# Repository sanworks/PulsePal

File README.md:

# PulsePal
Open source pulse train generator

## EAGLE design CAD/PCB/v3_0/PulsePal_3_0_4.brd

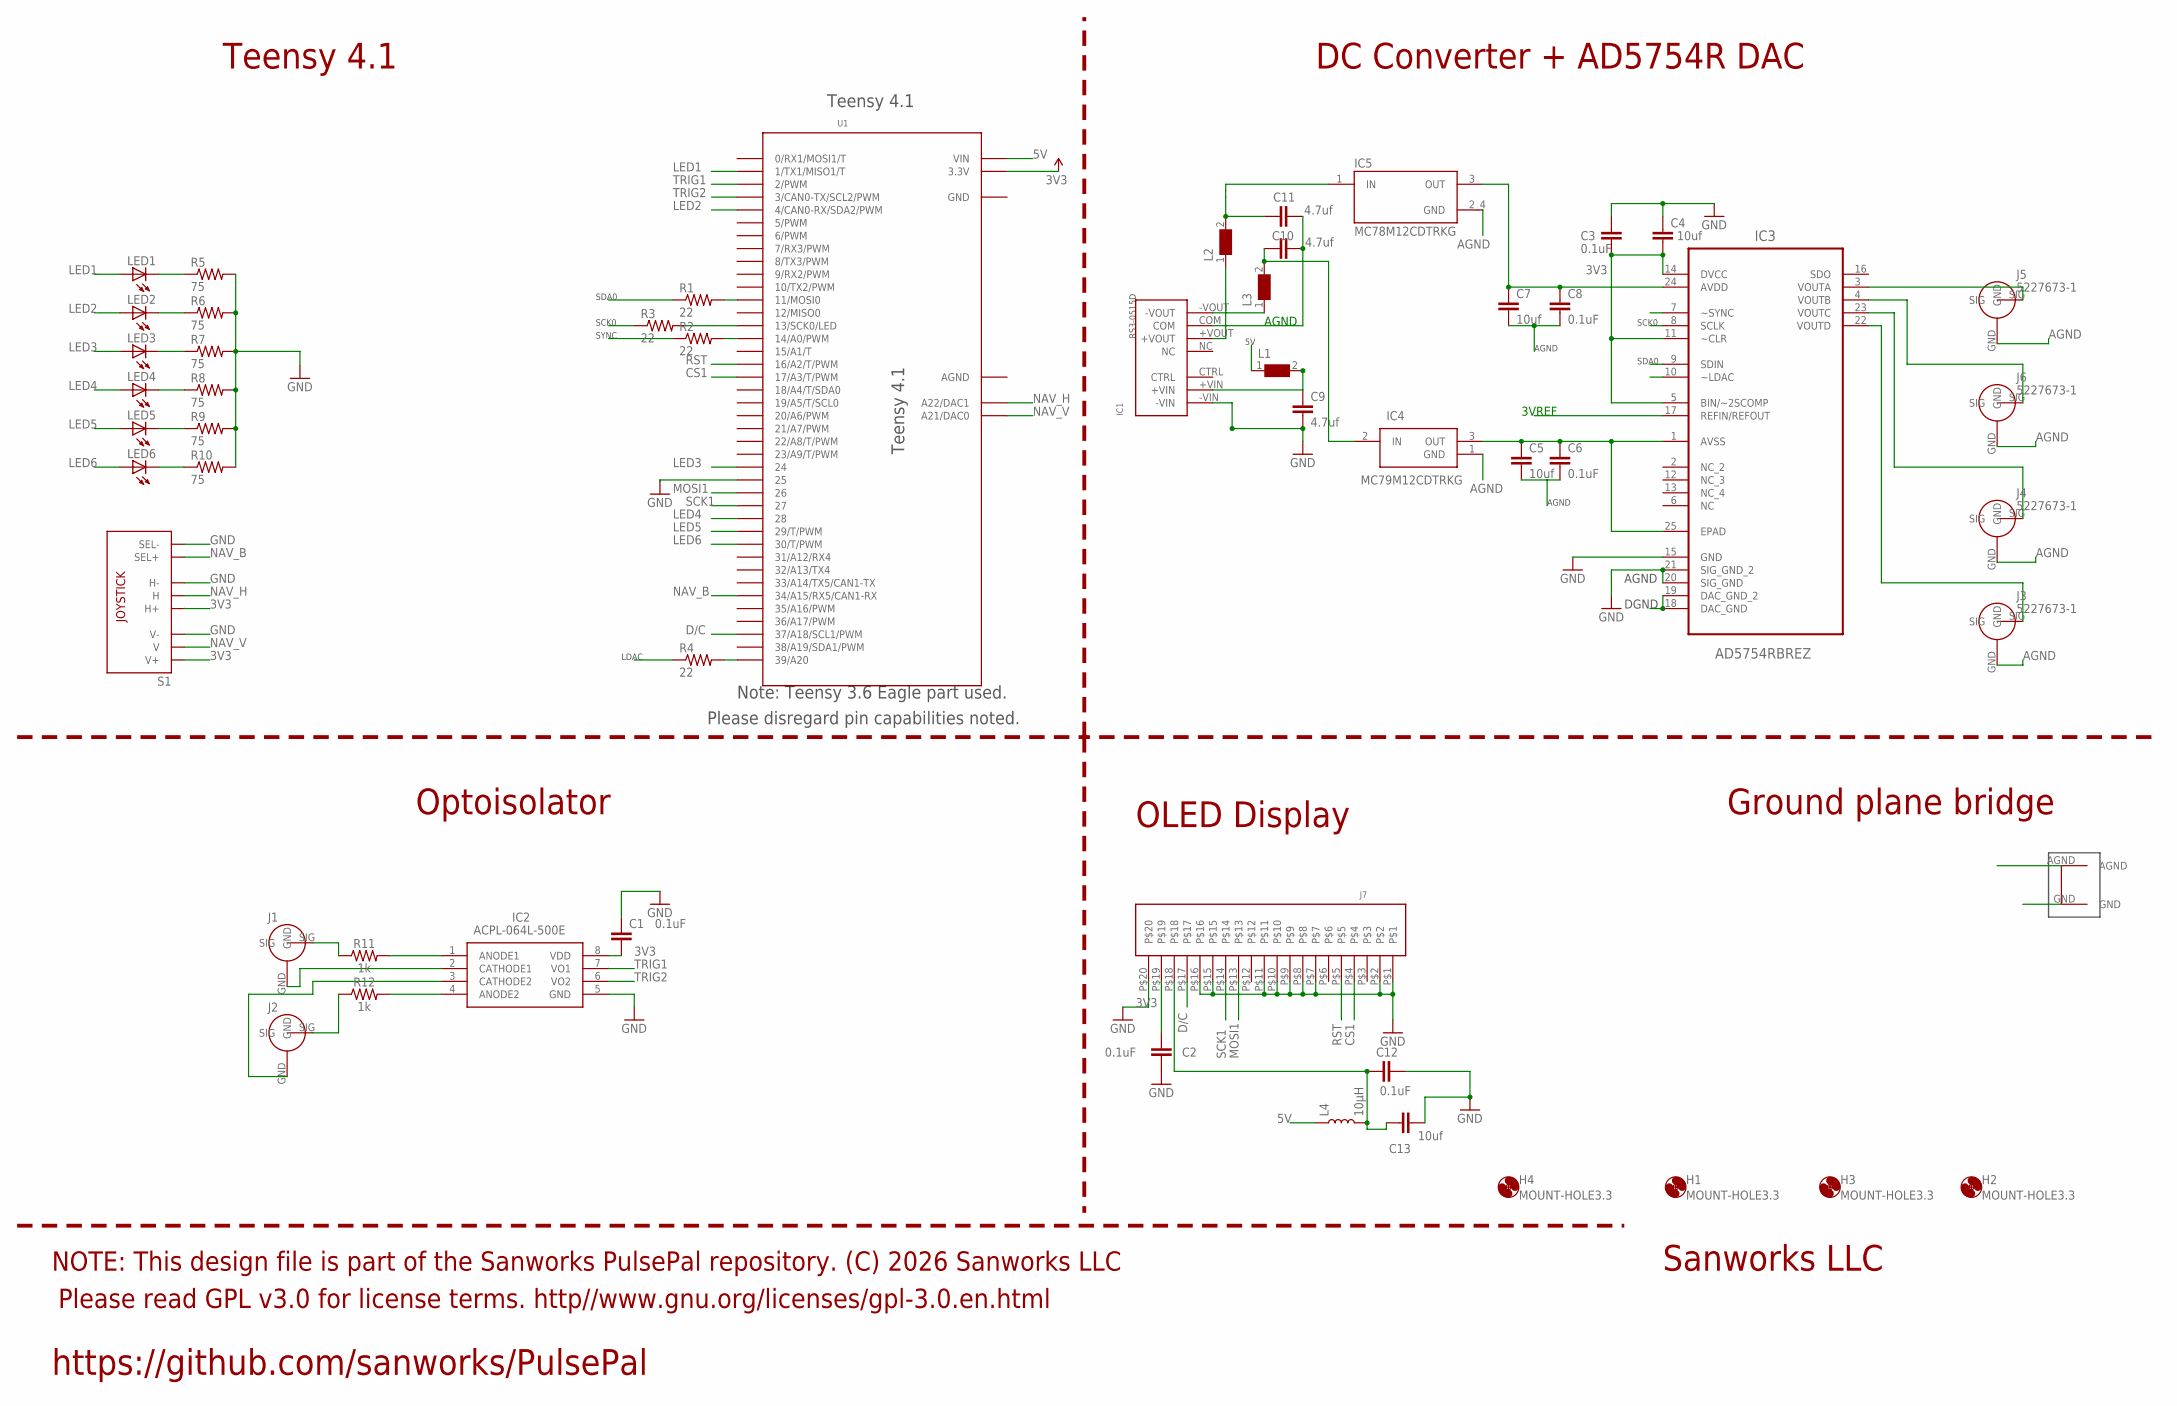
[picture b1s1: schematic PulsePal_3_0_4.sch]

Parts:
C1, C2, C3, C6, C8, C12: 0.1uF; 0805
C4, C5, C7, C13: 10uf; 1206@1
C9, C10, C11: 4.7uf; 1206@1
H1, H2, H3, H4: MOUNT-HOLE3.3; 3,3
IC1: RS3-0515D
IC2: ACPL-064L-500E; SOIC127P599X330-8N
IC3: AD5754RBREZ; SOP65P640X120-25N
IC4: MC79M12CDTRKG; NVD5117PLT4GVF01
IC5: MC78M12CDTRKG; VREG_MC78M12CDTRKG
J1, J2, J3, J4, J5, J6: 5227673-1; 52276731
J7: NHD-2.7-12864WDW3
L1, L2, L3: WE-CBF-742792118_1206; 1206
L4: 10μH; 0806
LED1, LED2, LED3, LED4, LED5, LED6: LEDCHIPLED_1206; CHIPLED_1206
R1, R2, R3, R4: 22; 1206
R5, R6, R7, R8, R9, R10: 75; 1206
R11, R12: 1k; 1206
S1: JOYSTICKPTH; JOYSTICK
U1: TEENSY_3.6_DIL
U$6: GNDPLANESHRT

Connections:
3V3: C1.2, C2.1, C3.2, C4.2, IC2.8 (VDD), IC3.5 (BIN/~2SCOMP), IC3.11 (~CLR), IC3.14 (DVCC), J7.P$19, S1.H1 (H+), S1.V1 (V+), U1.3.3V, U1.3.3V3 (3.3V)
3VREF: IC3.17 (REFIN/REFOUT)
5V: L1.1, L4.1, U1.VIN
AGND: C5.2, C6.2, C7.2, C8.2, C10.1, C11.2, IC1.COM, IC3.18 (DAC_GND), IC3.19 (DAC_GND_2), IC3.20 (SIG_GND), IC3.21 (SIG_GND_2), IC4.1 (GND), IC5.2_4 (GND), J3.GND, J4.GND, J5.GND, J6.GND, U1.AGND, U$6.AGND
CS1: J7.P$4, U1.17/A3 (17/A3/T/PWM)
D/C: J7.P$17, U1.37/A18 (37/A18/SCL1/PWM)
GND: C1.1, C2.2, C3.1, C4.1, C9.2, C12.2, C13.2, IC1.-VIN, IC2.5 (GND), IC3.15 (GND), J7.P$1, J7.P$2, J7.P$7, J7.P$8, J7.P$9, J7.P$10, J7.P$11, J7.P$15, J7.P$16, J7.P$20, R5.2, R6.2, R7.2, R8.2, R9.2, R10.2, S1.B2A (SEL-), S1.H3 (H-), S1.V3 (V-), U1.25, U1.GND, U1.GND1 (GND), U$6.GND
LDAC: IC3.10 (~LDAC), R4.1
LED1: LED1.A, U1.1 (1/TX1/MISO1/T)
LED2: LED2.A, U1.4 (4/CAN0-RX/SDA2/PWM)
LED3: LED3.A, U1.24
LED4: LED4.A, U1.28
LED5: LED5.A, U1.29 (29/T/PWM)
LED6: LED6.A, U1.30 (30/T/PWM)
MOSI1: J7.P$13, U1.26
unnamed: IC2.1 (ANODE1), R11.2
unnamed: J1.SIG, R11.1
unnamed: IC2.4 (ANODE2), R12.2
unnamed: J2.SIG, R12.1
unnamed: IC2.2 (CATHODE1), J1.GND
unnamed: IC2.3 (CATHODE2), J2.GND
unnamed: LED1.C, R5.1
unnamed: LED2.C, R6.1
unnamed: IC3.3 (VOUTA), J5.SIG
unnamed: IC3.4 (VOUTB), J6.SIG
unnamed: IC3.23 (VOUTC), J4.SIG
unnamed: IC3.22 (VOUTD), J3.SIG
unnamed: R1.2, U1.11 (11/MOSI0)
unnamed: R3.2, U1.13 (13/SCK0/LED)
unnamed: IC1.-VOUT, L3.1
unnamed: IC1.+VOUT, L2.1
unnamed: R2.2, U1.14/A0 (14/A0/PWM)
unnamed: R4.2, U1.39/A20
unnamed: LED3.C, R7.1
unnamed: LED4.C, R8.1
unnamed: LED5.C, R9.1
unnamed: LED6.C, R10.1
unnamed: C10.2, IC5.1 (IN), L2.2
unnamed: C11.1, IC4.2 (IN), L3.2
unnamed: C12.1, C13.1, J7.P$18, L4.2
unnamed: C9.1, IC1.+VIN, L1.2
NAV_B: S1.B1A (SEL+), U1.34/A15 (34/A15/RX5/CAN1-RX)
NAV_H: S1.H2 (H), U1.A22 (A22/DAC1)
NAV_V: S1.V2 (V), U1.A21 (A21/DAC0)
RST: J7.P$5, U1.16/A2 (16/A2/T/PWM)
SCK0: IC3.8 (SCLK), R3.1
SCK1: J7.P$14, U1.27
SDA0: IC3.9 (SDIN), R1.1
SYNC: IC3.7 (~SYNC), R2.1
TRIG1: IC2.7 (VO1), U1.2 (2/PWM)
TRIG2: IC2.6 (VO2), U1.3 (3/CAN0-TX/SCL2/PWM)
VDD: C7.1, C8.1, IC3.24 (AVDD), IC5.3 (OUT)
VSS: C5.1, C6.1, IC3.1 (AVSS), IC3.25 (EPAD), IC4.3 (OUT)

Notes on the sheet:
AGND
SCK0
SDA0
DGND
SYNC
LDAC
3VREF
Teensy 4.1
DC Converter + AD5754R DAC
Ground plane bridge
Please read GPL v3.0 for license terms. http//www.gnu.org/licenses/gpl-3.0.en.html
NOTE: This design file is part of the Sanworks PulsePal repository. (C) 2026 Sanworks LLC
Sanworks LLC
https://github.com/sanworks/PulsePal
Note: Teensy 3.6 Eagle part used.
Please disregard pin capabilities noted.
OLED Display
Optoisolator

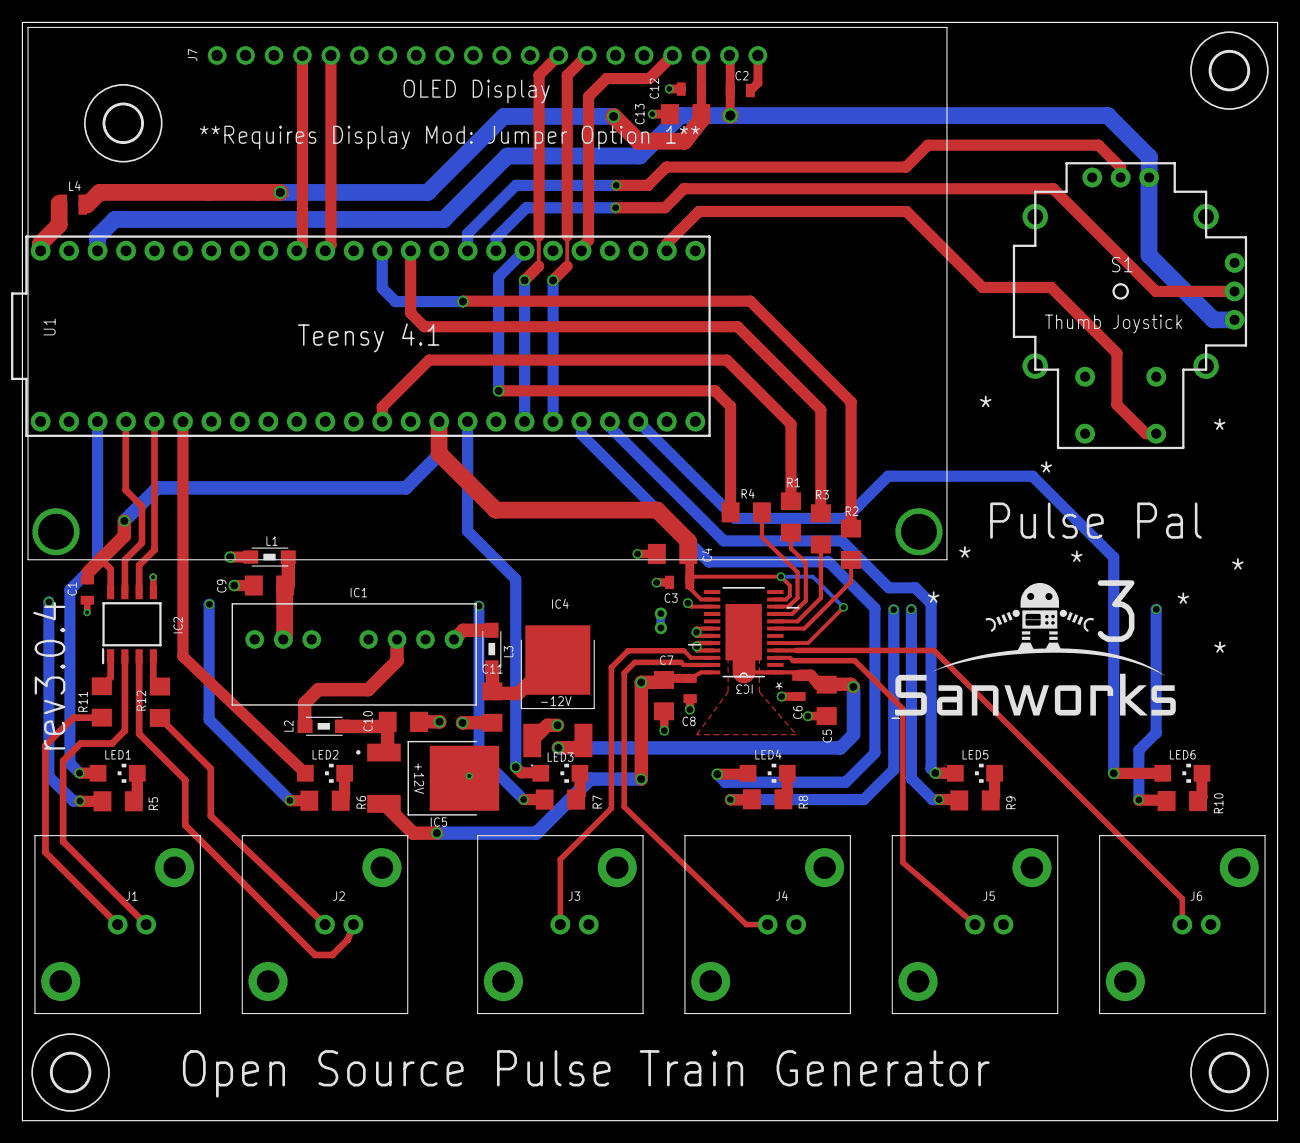
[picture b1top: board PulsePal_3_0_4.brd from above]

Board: 4 copper layers, 112.0 x 98.0 mm, 55 parts (0 on the bottom side), 52 nets.

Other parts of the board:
U$2: SANWORKS_LOGO

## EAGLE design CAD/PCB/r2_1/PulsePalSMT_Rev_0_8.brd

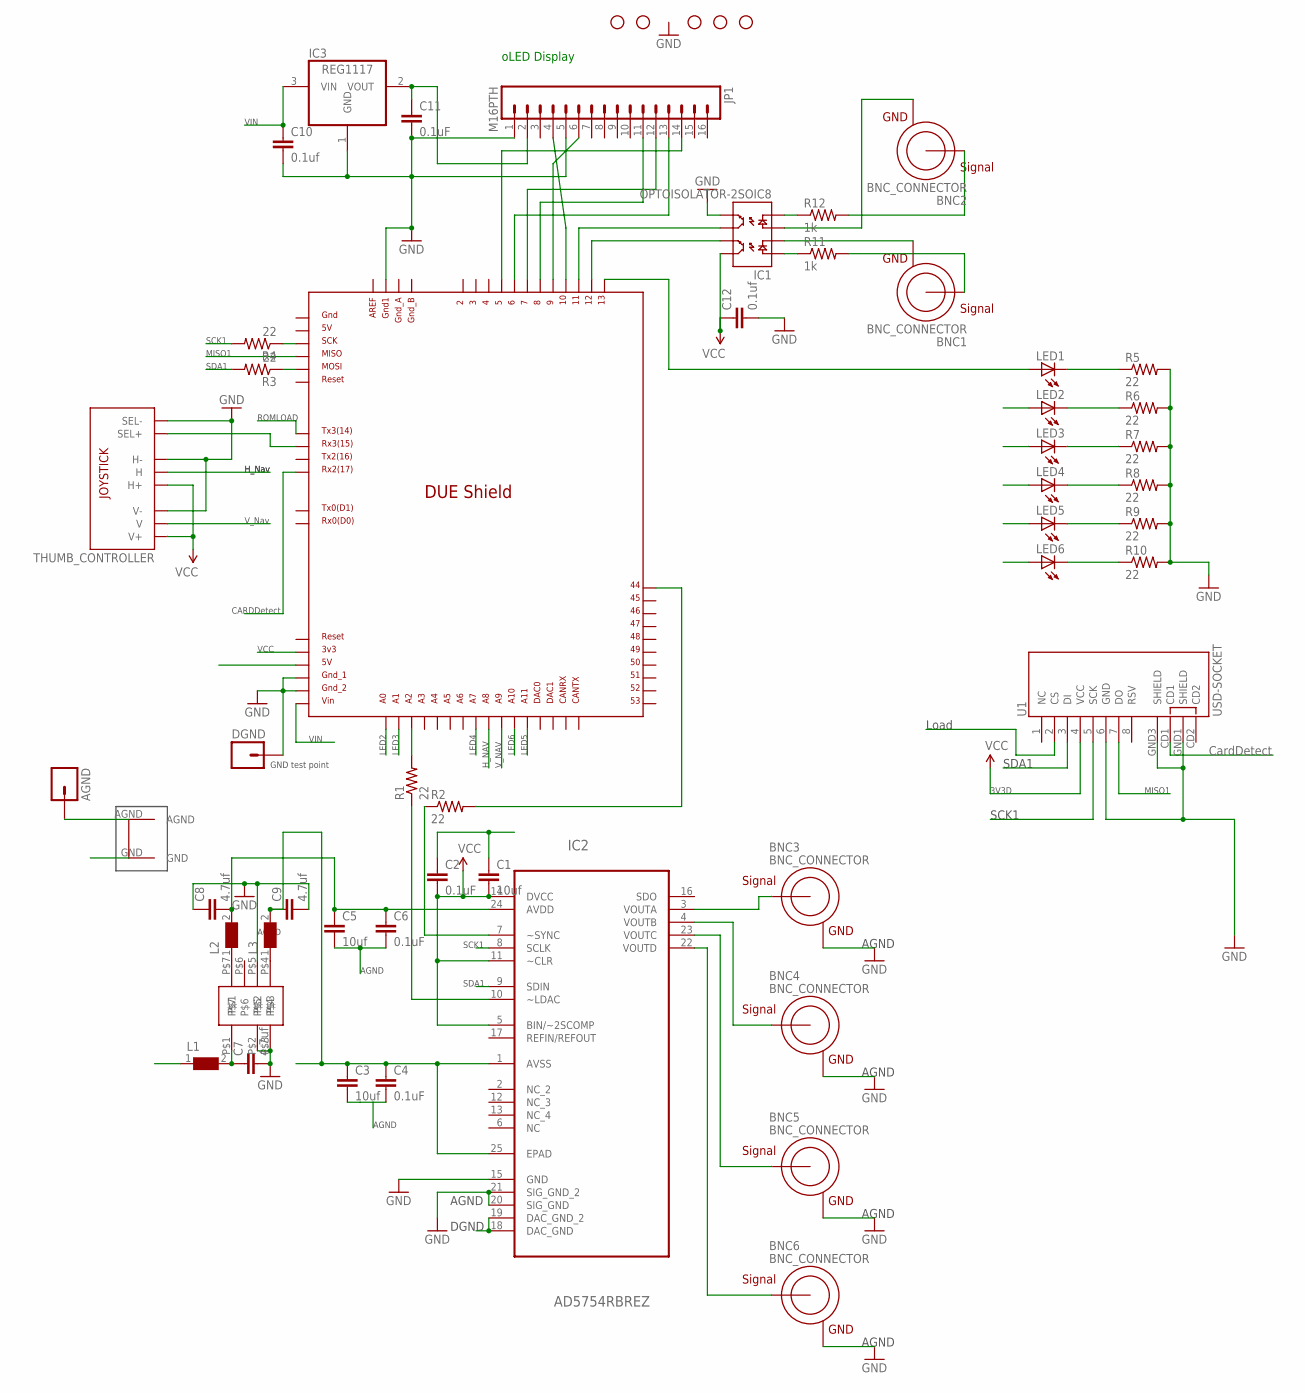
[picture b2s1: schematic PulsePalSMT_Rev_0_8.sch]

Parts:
AGND: M01PTH; 1X01
ARDUINO: DUE(NORMAL)
BNC1, BNC2, BNC3, BNC4, BNC5, BNC6: BNC_CONNECTOR
C1, C3, C5: 10uf; 1206@1
C2, C4, C6, C11: 0.1uF; 0805
C7, C8, C9: 4.7uf; 1206@1
C10: 0.1uf; 0805
C12: 0.1uf; 1206@1
DGND: M01PTH; 1X01
IC1: OPTOISOLATOR-2SOIC8; SO08-2
IC2: AD5754RBREZ; SOP65P640X120-25N
IC3: REG1117; SOT223
JP1: M16PTH; 1X16
JP2, JP5, JP6, JP8, JP9: STAND-OFF
L1, L2, L3: WE-CBF-742792118_1206; 1206
LED1, LED2, LED3, LED4, LED5, LED6: LEDCHIPLED_1206; CHIPLED_1206
R1, R2, R3, R4, R5, R6, R7, R8, R9, R10: 22; 1206
R11, R12: 1k; 1206
THUMB_CONTROLLER: JOYSTICKPTH; JOYSTICK
U1: USD-SOCKET; MICROSD_1:1
U2: TDK_LAMBDA_5_TO_BI_12_125MA
U$6: GNDPLANESHRT

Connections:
5V: ARDUINO.5V, C1.2, C2.2, IC2.5 (BIN/~2SCOMP), IC2.11 (~CLR), IC2.14 (DVCC), L1.1
AGND: AGND.1, BNC3.GND, BNC4.GND, BNC5.GND, BNC6.GND, C3.2, C4.2, C5.2, C6.2, IC2.15 (GND), IC2.18 (DAC_GND), IC2.19 (DAC_GND_2), IC2.20 (SIG_GND), IC2.21 (SIG_GND_2), U$6.AGND
CARDDETECT: ARDUINO.RX2, U1.CD1
GND: ARDUINO.GND1, ARDUINO.GND_1, ARDUINO.GND_2, C1.1, C2.1, C7.2, C8.1, C9.2, C10.2, C11.2, C12.2, DGND.1, IC1.5 (EM2), IC3.1 (GND), JP1.1, JP1.5, R5.2, R6.2, R7.2, R8.2, R9.2, R10.2, THUMB_CONTROLLER.B2A (SEL-), THUMB_CONTROLLER.H3 (H-), THUMB_CONTROLLER.V3 (V-), U1.6 (GND), U1.GND1 (SHIELD), U1.GND3 (SHIELD), U2.P$2, U2.P$3, U2.P$5, U$6.GND
H_NAV: ARDUINO.A8, THUMB_CONTROLLER.H2 (H)
LED2: ARDUINO.A0, LED2.A
LED3: ARDUINO.A1, LED3.A
LED4: ARDUINO.A7, LED4.A
LED5: ARDUINO.A11, LED5.A
LED6: ARDUINO.A10, LED6.A
MISO1: ARDUINO.MISO_ICSP, U1.7 (DO)
unnamed: L2.1, U2.P$7
unnamed: L3.1, U2.P$4
unnamed: BNC3.SIGNAL, IC2.3 (VOUTA)
unnamed: BNC4.SIGNAL, IC2.4 (VOUTB)
unnamed: BNC5.SIGNAL, IC2.23 (VOUTC)
unnamed: BNC6.SIGNAL, IC2.22 (VOUTD)
unnamed: BNC1.GND, IC1.2 (C1)
unnamed: BNC1.SIGNAL, R11.2
unnamed: BNC2.GND, IC1.3 (A2)
unnamed: BNC2.SIGNAL, R12.2
unnamed: ARDUINO.SCK_ICSP, R4.1
unnamed: ARDUINO.MOSI_ICSP, R3.1
unnamed: ARDUINO.44, R2.2
unnamed: ARDUINO.A2, R1.2
unnamed: IC2.7 (~SYNC), R2.1
unnamed: IC2.10 (~LDAC), R1.1
unnamed: ARDUINO.RX3, THUMB_CONTROLLER.B1A (SEL+)
unnamed: ARDUINO.11, IC1.6 (CL2)
unnamed: C11.1, IC3.2 (VOUT), JP1.2
unnamed: LED1.C, R5.1
unnamed: LED2.C, R6.1
unnamed: LED3.C, R7.1
unnamed: LED4.C, R8.1
unnamed: LED5.C, R9.1
unnamed: LED6.C, R10.1
unnamed: IC1.1 (A1), R11.1
unnamed: IC1.4 (C2), R12.1
unnamed: ARDUINO.12, IC1.7 (EM1)
unnamed: ARDUINO.5, JP1.14
unnamed: ARDUINO.13, LED1.A
unnamed: ARDUINO.10, JP1.4
unnamed: ARDUINO.9, JP1.6
unnamed: ARDUINO.8, JP1.11
unnamed: ARDUINO.7, JP1.12
unnamed: ARDUINO.6, JP1.13
unnamed: C5.1, C6.1, C8.2, IC2.24 (AVDD), L2.2
unnamed: C3.1, C4.1, C9.1, IC2.1 (AVSS), IC2.25 (EPAD), L3.2
unnamed: C7.1, L1.2, U2.P$1
ROMLOAD: ARDUINO.TX3, U1.2 (CS)
SCK1: IC2.8 (SCLK), R4.2, U1.5 (SCK)
SDA1: IC2.9 (SDIN), R3.2, U1.3 (DI)
VCC: ARDUINO.3V3, C12.1, IC1.8 (CL1), THUMB_CONTROLLER.H1 (H+), THUMB_CONTROLLER.V1 (V+), U1.4 (VCC)
VIN: ARDUINO.VIN, C10.1, IC3.3 (VIN)
V_NAV: ARDUINO.A9, THUMB_CONTROLLER.V2 (V)

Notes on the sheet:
oLED Display
AGND
SCK1
SDA1
DGND
VCC
ROMLOAD
LED2
LED3
LED4
LED5
LED6
GND test point
H_Nav
V_Nav
MISO1
H_NAV
V_NAV
VIN
3V3D
Load
CardDetect
CARDDetect

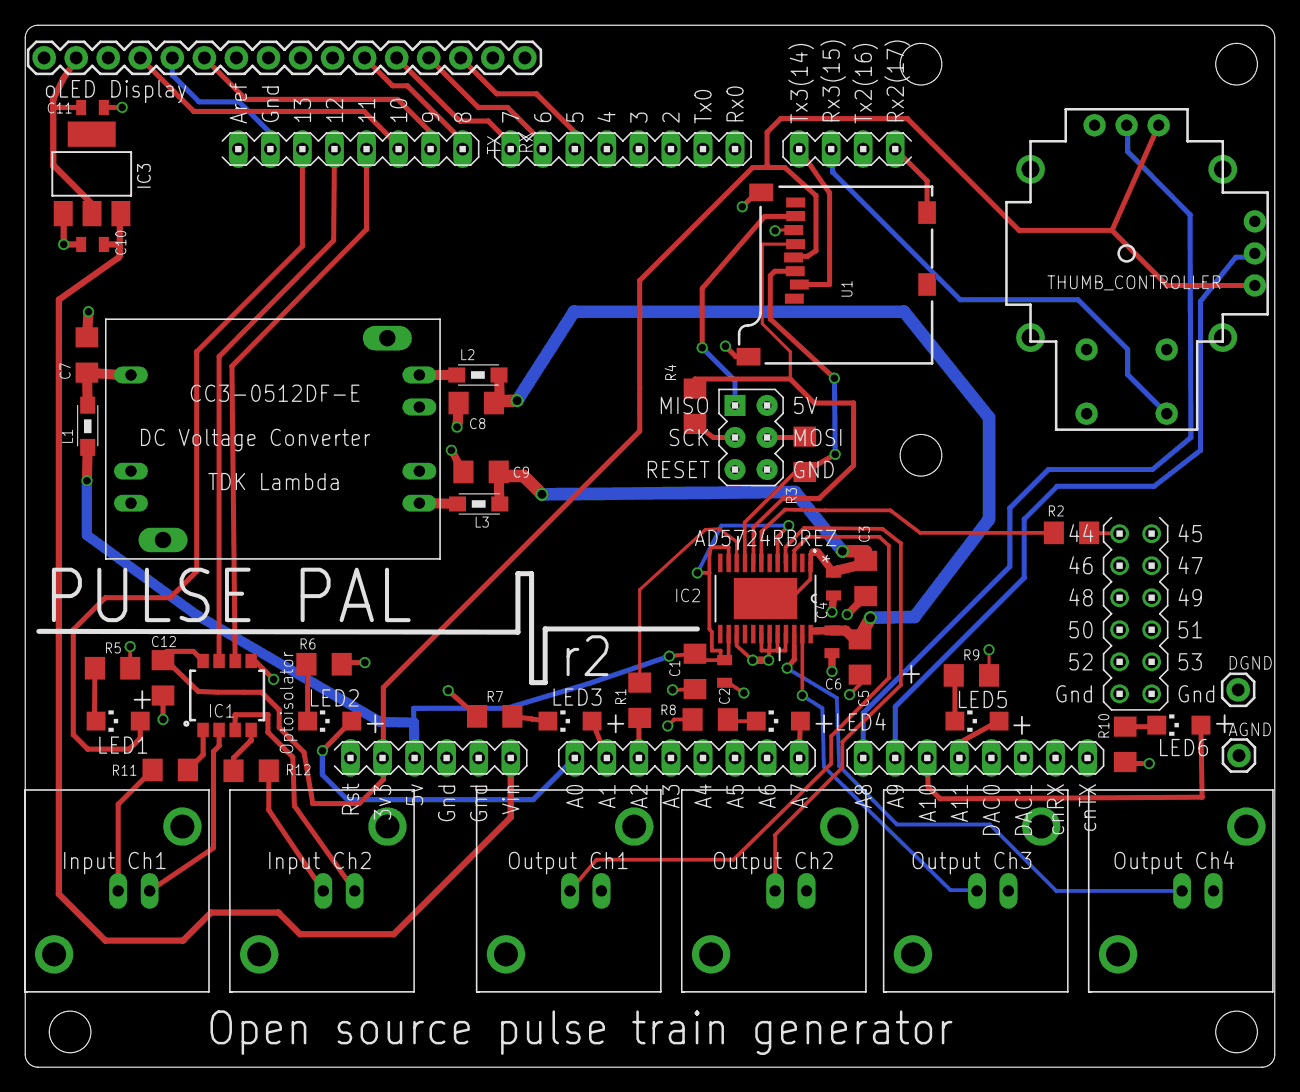
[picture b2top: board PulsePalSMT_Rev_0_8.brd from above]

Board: 4 copper layers, 99.0 x 82.6 mm, 55 parts (0 on the bottom side), 55 nets.

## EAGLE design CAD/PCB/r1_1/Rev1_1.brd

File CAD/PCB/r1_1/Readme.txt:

----------------------------------------------------------------------------

The files in this folder are part of the Sanworks Pulse Pal repository
Copyright (C) 2016 Sanworks LLC, Sound Beach, New York, USA

----------------------------------------------------------------------------

These design files are free software: you can redistribute and/or modify
them under the terms of the GNU General Public License as published by
the Free Software Foundation, version 3.

These files are distributed  WITHOUT ANY WARRANTY and without even the 
implied warranty of MERCHANTABILITY or FITNESS FOR A PARTICULAR PURPOSE.  
See the GNU General Public License for more details.

You should have received a copy of the GNU General Public License
along with these files. If not, see <http://www.gnu.org/licenses/>.

-----------------------------------------------------------------------------

*Instructions*

The schematic Rev_X.X.sch,
and the circuit board design file Rev_X.X.brd,
can be opened with Cadsoft Eagle:
http://www.cadsoftusa.com/

The GERBER files are pre-compiled CAM files for circuit board manufacturing with SeeedStudio's fusion PCB service.
USA: http://www.seeedstudio.com/service/index.php?r=upcb
Global: http://www.seeedstudio.com/service/index.php?r=pcb

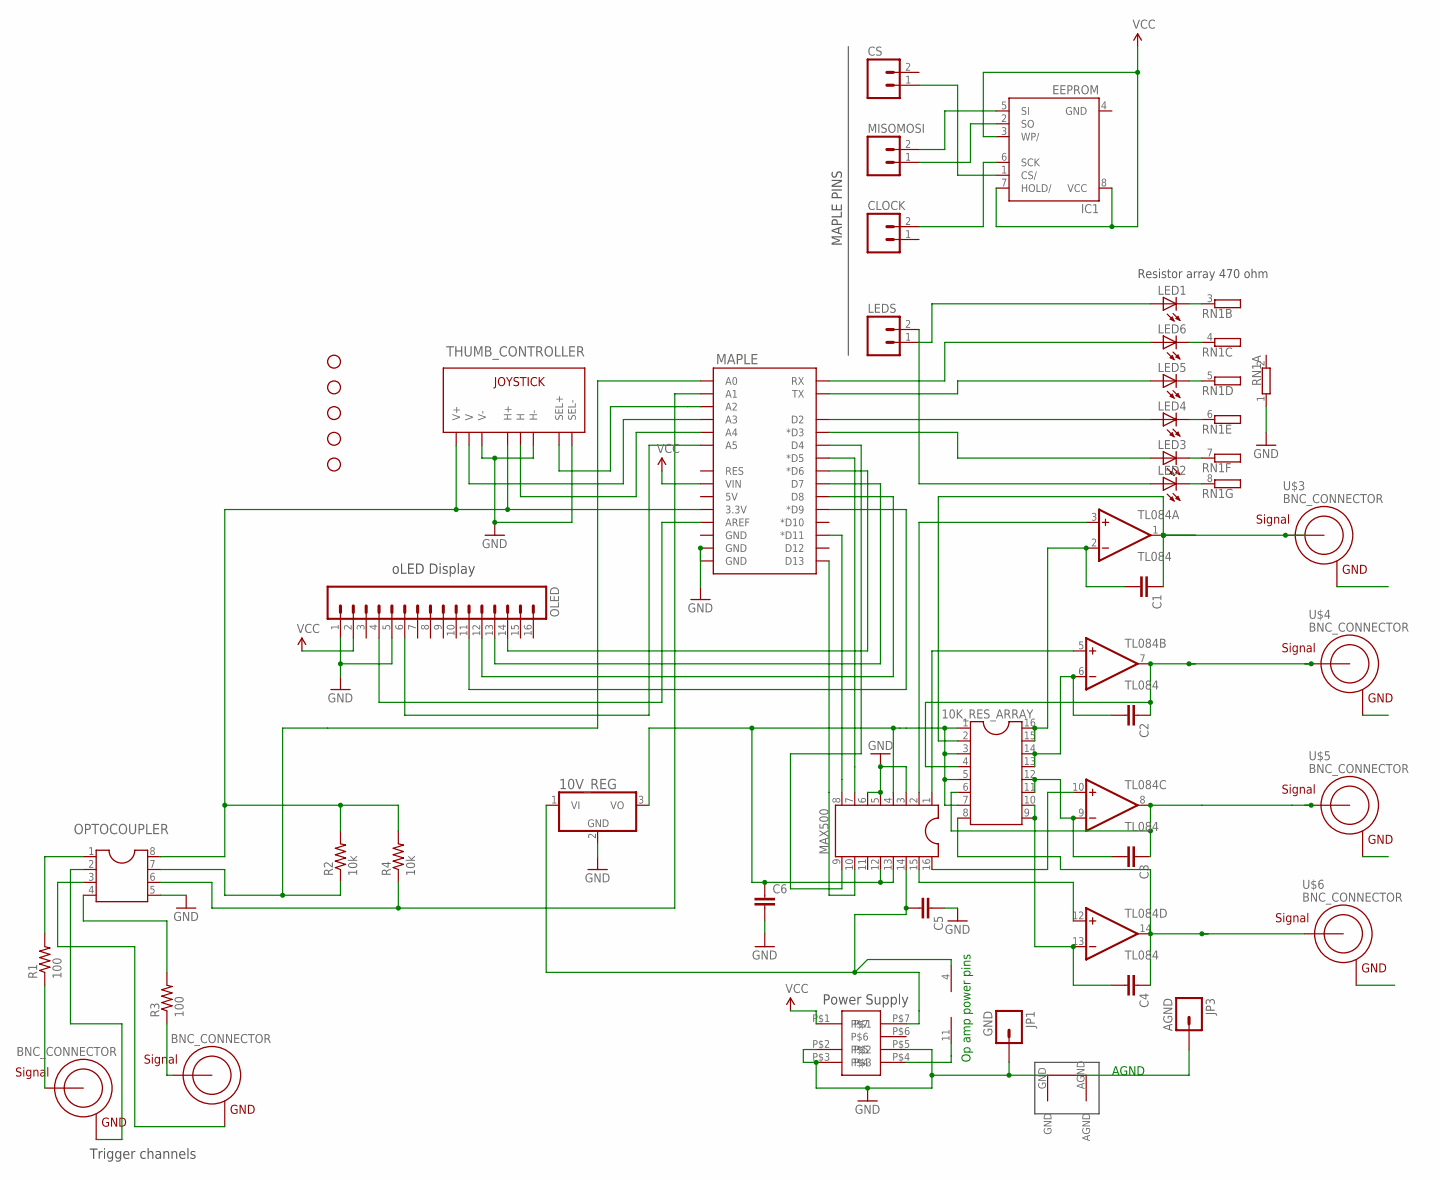
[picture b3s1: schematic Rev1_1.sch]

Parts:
10K_RES_ARRAY: DIL16
10V_REG: 7805T; TO220H
C1, C2, C3, C4, C5, C6: CAPPTH; CAP-PTH-SMALL
CLOCK: M02PTH; 1X02
CS: M02PTH; 1X02
IC1: EEPROM; DIL08
JP1: GND; 1X01
JP2, JP5, JP6, JP8, JP9: STAND-OFF
JP3: AGND; 1X01
LED1, LED2, LED3, LED4, LED5, LED6: LED3MM
LEDS: M02PTH; 1X02
MAPLE: ARDUINO_SHIELDNOHOLESORLABELS; DUEMILANOVE_SHIELD_NOHOLES_NOLABELS
MAX500: DIL16
MISOMOSI: M02PTH; 1X02
OLED: M16PTH; 1X16
OPTOCOUPLER: DIL8; DIL08
R1, R3: 100; AXIAL-0.3
R2, R4: 10k; AXIAL-0.3
RN1: GE07R; SIL8
THUMB_CONTROLLER: JOYSTICKPTH; JOYSTICK
TL084: TL084; DIL14
U$1, U$2, U$3, U$4, U$5, U$6: BNC_CONNECTOR
U$7: GNDPLANESHRT
U$8: TDK_LAMBDA_5_TO_BI_12_125MA

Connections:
AGND: JP3.1, U$3.GND, U$4.GND, U$5.GND, U$6.GND, U$7.AGND
GND: 10V_REG.2 (GND), C5.1, C6.2, IC1.4 (GND), JP1.1, MAPLE.GND@0 (GND), MAPLE.GND@1 (GND), MAX500.3, MAX500.5, MAX500.6, OLED.1, OLED.5, OPTOCOUPLER.5, RN1.1, THUMB_CONTROLLER.B2A (SEL-), THUMB_CONTROLLER.H3 (H-), THUMB_CONTROLLER.V3 (V-), U$7.GND, U$8.P$2, U$8.P$3, U$8.P$5
unnamed: LED6.A, MAPLE.RX
unnamed: LED5.A, MAPLE.TX
unnamed: LED4.A, MAPLE.D2
unnamed: LED3.A, MAPLE.D3 (*D3)
unnamed: MAPLE.D11 (*D11), MAX500.8
unnamed: MAPLE.D13, MAX500.10
unnamed: MAPLE.AREF, OLED.4
unnamed: MAPLE.D4, MAX500.9
unnamed: MAPLE.D5 (*D5), MAX500.7
unnamed: MAPLE.D6 (*D6), OLED.14
unnamed: MAPLE.D7, OLED.13
unnamed: MAPLE.D8, OLED.12
unnamed: MAPLE.D9 (*D9), OLED.11
unnamed: MAPLE.A5, OLED.6
unnamed: MAPLE.A4, THUMB_CONTROLLER.H2 (H)
unnamed: MAPLE.A3, THUMB_CONTROLLER.V2 (V)
unnamed: MAPLE.A2, THUMB_CONTROLLER.B1A (SEL+)
unnamed: R1.P$1 (1), U$1.SIGNAL
unnamed: MAPLE.A0, OPTOCOUPLER.7, R2.P$1 (1)
unnamed: R3.P$1 (1), U$2.SIGNAL
unnamed: MAPLE.A1, OPTOCOUPLER.6, R4.P$1 (1)
unnamed: TL084.11 (V-), U$8.P$4
unnamed: MAX500.2, TL084.3 (+IN)
unnamed: MAX500.1, TL084.5 (+IN)
unnamed: 10V_REG.1 (VI), C5.2, MAX500.14, TL084.4 (V+), U$8.P$7
unnamed: 10K_RES_ARRAY.1, 10K_RES_ARRAY.3, 10K_RES_ARRAY.5, 10K_RES_ARRAY.7, 10V_REG.3 (VO), C6.1, MAX500.4, MAX500.12, MAX500.13
unnamed: MAX500.16, TL084.10 (+IN)
unnamed: MAX500.15, TL084.12 (+IN)
unnamed: 10K_RES_ARRAY.2, C1.1, TL084.1 (OUT), U$3.SIGNAL
unnamed: 10K_RES_ARRAY.4, C2.1, TL084.7 (OUT), U$4.SIGNAL
unnamed: 10K_RES_ARRAY.6, C3.1, TL084.8 (OUT), U$5.SIGNAL
unnamed: 10K_RES_ARRAY.8, C4.1, TL084.14 (OUT), U$6.SIGNAL
unnamed: LED1.A, LEDS.1
unnamed: LED2.A, LEDS.2
unnamed: LED2.K (C), RN1.8 (2)
unnamed: LED3.K (C), RN1.7 (2)
unnamed: LED4.K (C), RN1.6 (2)
unnamed: LED5.K (C), RN1.5 (2)
unnamed: LED6.K (C), RN1.4 (2)
unnamed: 10K_RES_ARRAY.15, 10K_RES_ARRAY.16, C1.2, TL084.2 (-IN)
unnamed: 10K_RES_ARRAY.13, 10K_RES_ARRAY.14, C2.2, TL084.6 (-IN)
unnamed: 10K_RES_ARRAY.11, 10K_RES_ARRAY.12, C3.2, TL084.9 (-IN)
unnamed: 10K_RES_ARRAY.9, 10K_RES_ARRAY.10, C4.2, TL084.13 (-IN)
unnamed: LED1.K (C), RN1.3 (2)
unnamed: OPTOCOUPLER.1, R1.P$2 (2)
unnamed: CS.1, IC1.1 (CS/)
unnamed: IC1.5 (SI), MISOMOSI.2
unnamed: IC1.2 (SO), MISOMOSI.1
unnamed: CLOCK.2, IC1.6 (SCK)
unnamed: OPTOCOUPLER.2, U$1.GND
unnamed: OPTOCOUPLER.4, R3.P$2 (2)
unnamed: OPTOCOUPLER.3, U$2.GND
unnamed: MAPLE.3.3V, OPTOCOUPLER.8, R2.P$2 (2), R4.P$2 (2), THUMB_CONTROLLER.H1 (H+), THUMB_CONTROLLER.V1 (V+)
VCC: IC1.3 (WP/), IC1.7 (HOLD/), IC1.8 (VCC), MAPLE.VIN, OLED.2, U$8.P$1

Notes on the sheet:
oLED Display
Power Supply
Op amp power pins
MAPLE PINS
Trigger channels
Resistor array 470 ohm
AGND

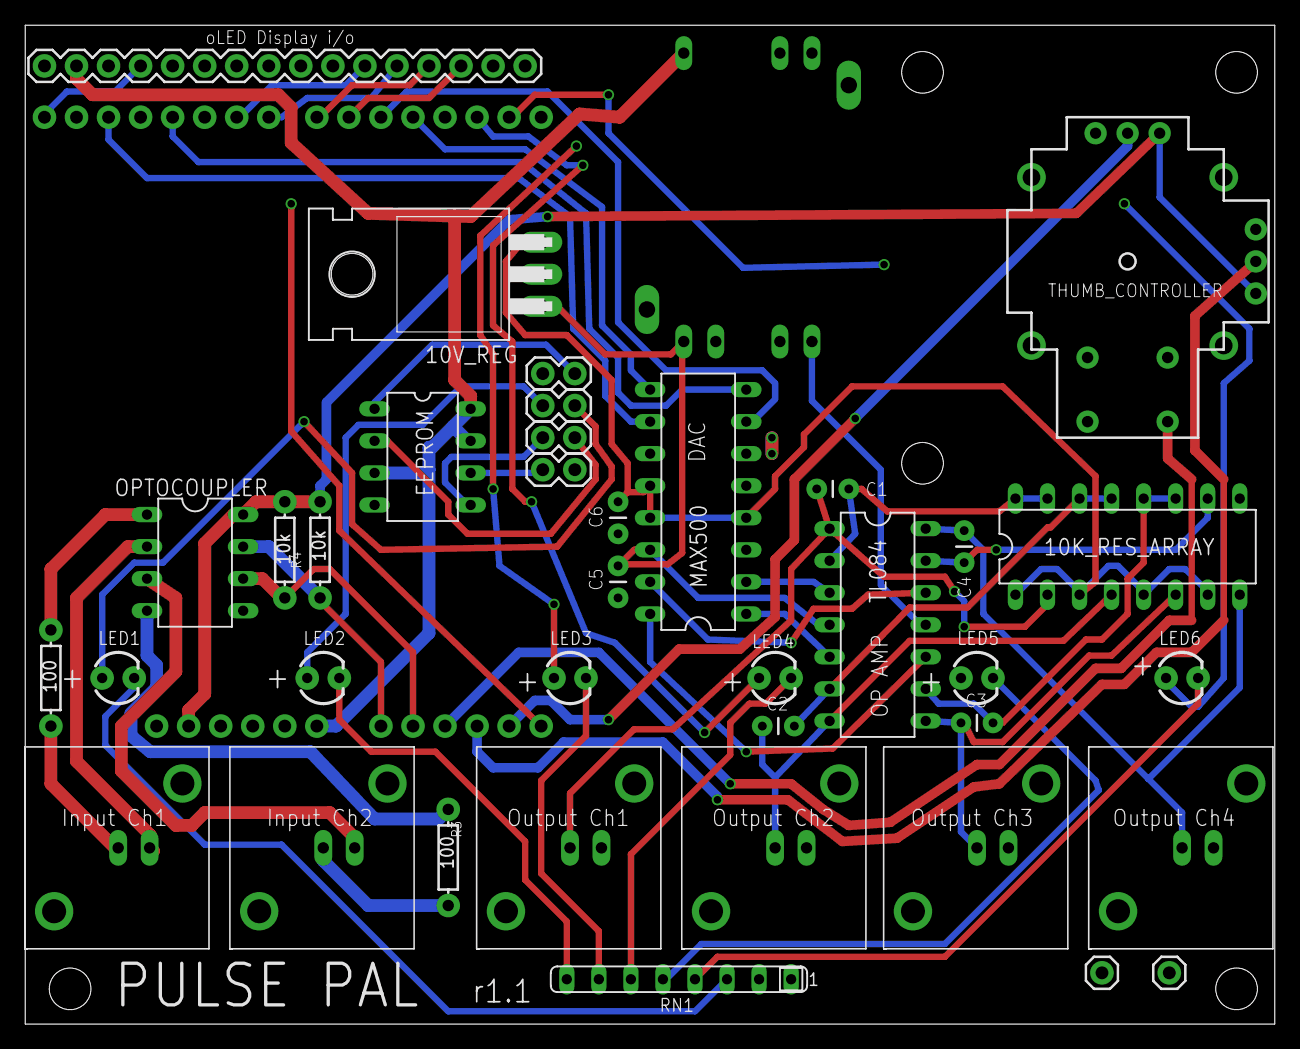
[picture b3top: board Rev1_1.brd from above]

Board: 4 copper layers, 99.0 x 79.2 mm, 45 parts (1 on the bottom side), 56 nets.

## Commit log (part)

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2016-03-02 Added support for GNU Octave 4 Added struct based parameters for MATLAB API Included more intuitive soft-trigger syntax for MATLAB API
2016-03-02 In MATLAB client, ProgramPulsePalParam now updates the Params struct with the new parameter after programming
2016-03-03 Fixed screen saver timing in v1.1 firmware
2016-03-28 Added support for Pulse Pal 2 on Python When settings are loaded from SD card using a software command, the settings are now read back from the device and pushed to MATLAB and Python parameter fields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
2016-04-16 Added C++ support for Pulse Pal 2 Added PCB design files for Pulse Pal 1.1 and 2 Added drivers for Pulse Pal 2 Added microSD file delete option in MATLAB for Pulse Pal 2 Fixed a bug in new trigger sy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
2016-04-19 -Added support for deleting microSD settings files from thumb joystick menu -Added more comments to Pulse Pal 2 firmware -Increased custom pulse limit to 5000 for Pulse Pal 2 -Renamed SetContinuousLo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
2016-04-19 -Restored functionality to thumb joystick "single pulse" option -Corrected default parameters in MATLAB client to match firmware
2016-04-22 -Added more code comments -Bug fix: Digit-wise voltage adjustment from thumb menu fixed to account for -0, restoring access to the range -1V to 0V -Bug fix: Added flag for DAC update when setting res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
2016-06-14 Firmware update - changed boot sequence to set DAC outputs to resting voltage immediately on power-up. Previous firmware versions had taken ~1ms to do so. This firmware version takes 10 microseconds 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
2016-07-15 -Removed PulsePalGUI.m pointing to PulsePalProgramGUI -Renamed MATLAB GUI file from PulsePalProgramGUI to PulsePalGUI
2016-08-17 -Added alternative firmware for use as a waveform generator (alpha) -Added new object-oriented MATLAB APIs for Pulse Pal and the waveform generator -Changed how data is sent when programming all para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
2016-08-22 -Updated Python API to use ArCOM functions
2016-09-30 Fixed voltage conversion in ProgramPulsePalParam for Pulse Pal 2
2016-10-06 Revised Pulse Pal 2.0 PCB design: -Improved ground trace layout near DAC -Added filtering capacitor on oLED screen voltage regulator
2017-05-05 -Fixed behavior of "pulse gated" mode when used with both trigger channels simultaneously -Updated firmware to use union for integer type conversion and SPI array writes for efficiency (frees CPU for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
2017-06-22 bug fix in voltage output function "setFixedVoltage" (for Pulse Pal 2)
    Corrected the order of two Bytes in message containing voltage value.
    Tested on Pulse Pal 2 in firmware version 20
2017-08-23 -Updated serial port auto-detection for Windows 10 + Matlab r2017a
2017-10-18 -Added updated Pulse Pal 2 PCB design
2020-03-13 Convert to Python 3
    Also a few cleanups
2020-08-25 -Removed SDFatUtil dependency (not required with current version of SDFat)
2021-05-18 -Ported Python API from Python2 to Python3.
2023-09-27 -Python3: in sendCustomPulseTrain() and sendCustomWaveform() methods, added support for times and voltages given as numpy nd-array -Python3: Fixed a typo in the example code
2023-11-03 -Fixed repo issue#2, Rounding of numbers (Phase1Duration). Thanks to Christian Skoven for pointing it out! -Python: Reformatted PulsePalObject class and added docstrings to improve clarity -Python: U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
2023-11-19 -Added code of conduct
2023-11-19 -Added contributor guidelines
2024-02-05 -MATLAB: Updated serial interface to use MATLAB's serialport class instead of serial or PsychToolbox IOPORT on r2019b or newer. -MATLAB: Updated USB serial port discovery to use MATLAB's serialportli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
2024-02-05 -Removed last serial port used
2024-02-07 -Updated wiki link in readme
2024-02-07 -Python3: Added set2DefaultParams(), a method to return Pulse Pal to the default parameters initially set on initializing a PulsePal object. -Fixed case typo in example code
2024-02-07 -Python3: Added function header comment to set2DefaultParams
2024-02-07 -Python3: Removed auto-sync from new set2DefaultParams() function.
2024-02-16 -Removed port COM1 on Windows. USB port assignments begin with COM3
2024-04-24 -GenerateZeroPhaseSineWave: Fixed bug processing optional sampling rate arg
2024-04-26 -GenerateZeroPhaseSineWave: Removed obsolete size check
2024-10-17 -Readme: updated link to original project
2025-07-18 -Added Pulse Pal firmware v3 (likely very buggy)
2025-07-18 -Firmware: Added channel mapping to support hardware v3 -MATLAB software: Handled firmware v22
2025-07-18 -Firmware: Fixed microSD support and software reset functions on hardware v3
2025-07-18 -Firmware: Fixed text centering and cursor behavior on hardware v3
2025-08-28 -Firmware: Fixed oLED current draw issue on Pulse Pal 3 -Firmware: Fixed screen-clearing on each thumb joystick nav event -Firmware: Added Sanworks logo
2025-08-28 -Firmware: Restored support for HW v2
2025-10-31 -Pulse Pal 3 firmware: updated splash screen
2025-11-06 - Firmware: Added improved data transfer methods - Firmware: Added macro for max custom pulse limit (HW dependent) - Firmware: Routed USB Serial via ArCOM - MATLAB software: Added a new class to inte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
2025-11-07 -Firmware: Fixed timer callback interference with main-loop USB data transfer. USB op menu is now called from main loop. -Firmware: Minor optimizations to ArCOM
2025-11-07 -Firmware: Removed CycleDuration variable, redundant with TIMER_PERIOD macro. CycleFrequency is now calculated from Timer_PERIOD. -Firmware: Added additional hardware info returned from op 94 - MATLA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
2025-11-07 -Added support for 4 custom pulse trains on HW v3, and the possibility to add more by setting N_CUSTOM_PULSE_TRAINS in firmware
2025-11-07 -Firmware: Fixed limit on range of custom train ID
2025-11-13 -Firmware: Updated license info, small tweak to data transfer
2025-11-13 - Firmware: Renamed firmware folders to match actual target hardware - MATLAB class: Added support for firmware v22 on HW v2
2025-12-04 -Firmware: Fixed op 78 (display text to screen) -MATLAB interface (legacy): Fixed EndPulsePal, added hardware information request to init process if new firmware detected
2026-01-07 -MATLAB PulsePalDevice: Created class folder for better organization -MATLAB PulsePalDevice: Added GUI (layout complete, not yet functional)
2026-05-28 -MATLAB: PulsePalDevice GUI Updates. All parameter fields now sync with the GUI's internal values. Custom waveform data is not yet handled.
2026-05-29 -MATLAB GUI: Added support for entering custom trains
2026-05-29 -MATLAB GUI: Added feature to restore defaults.
2026-06-01 -MATLAB GUI: Added function to sync GUI parameters and custom trains to device
2026-06-03 -MATLAB GUI: Added ability to open and save programs -MATLAB GUI: Added status bar
2026-06-04 -MATLAB GUI: Restored support for r2020b and newer -MATLAB GUI: Added feature to automatically close GUI when its linked PulsePalDevice instance is cleared in r2024b and newer -MATLAB GUI: Fixed bug 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
2026-06-05 -MATLAB Class: Fixed several minor bugs -MATLAB Class: Improved code comments and formatting -MATLAB Class: Moved constants into separate block and applied naming convention -MATLAB Class: Changed au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
2026-06-05 -MATLAB Class: Fixed destructor to ensure that both commands previously in one in try/fail block are actually run
2026-06-05 - Added DAC Zero-code error calibration to firmware and MATLAB software. Calibration is stored in EEPROM. - Firmware: Fixed a bug where ch4 would not always update due to timing of LDAC on hardware v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
2026-06-09 - Firmware and MATLAB class: Added new operation to format the microSD card
2026-06-09 -Firmware: Added device info screen to menu, which displays hardware and firmware versions
2026-06-11 -Added Pulse Pal 3 CAD files for PCB and enclosure -Reorganized MATLAB folder to ensure that legacy interface is clearly noted as such -Firmware: Fixes to compile for Pulse Pal 2
2026-06-11 -Firmware: Fixed bug where first pulse triggered from thumb joystick menu could be up to 50us too short. Bug did not affect playback when triggered from TTL or API. -Firmware: Joystick menu playback 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
2026-06-11 -Firmware: Fixed type declaration
2026-06-19 -Firmware: Fixed bug re: filenames
2026-06-21 -MATLAB: Added a UI-driven firmware loading tool
2026-06-21 -Python interface: Depricated the existing interfaces and added a new one that is pep8 compliant, modern and more efficient
2026-06-25 -Python: Added methods to sync parameters from device, load/save/delete microSD settings and format the microSD card -Python: Updated trigger_outputs() to accept a single channel or lists of channels
2026-06-25 -Firmware: Reset joystick menu level when connecting to app
2026-06-26 -MATLAB: Updated firmware binaries -Python: Reorganized class to group info fields into a dataclass and make constants private
2026-06-26 -Python: Added calibration method -Python: Added close op to exit and del functions -MATLAB: Renamed calibration method

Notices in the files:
parts and their libraries:
SparkFun-Connectors: Licensing: Creative Commons ShareAlike 4.0 International - https://creativecommons.org/licenses/by-sa/4.0
